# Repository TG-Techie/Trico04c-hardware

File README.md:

# Trico04c-hardware
published under : Attribution-NonCommercial 3.0 United States (CC BY-NC 3.0 US)

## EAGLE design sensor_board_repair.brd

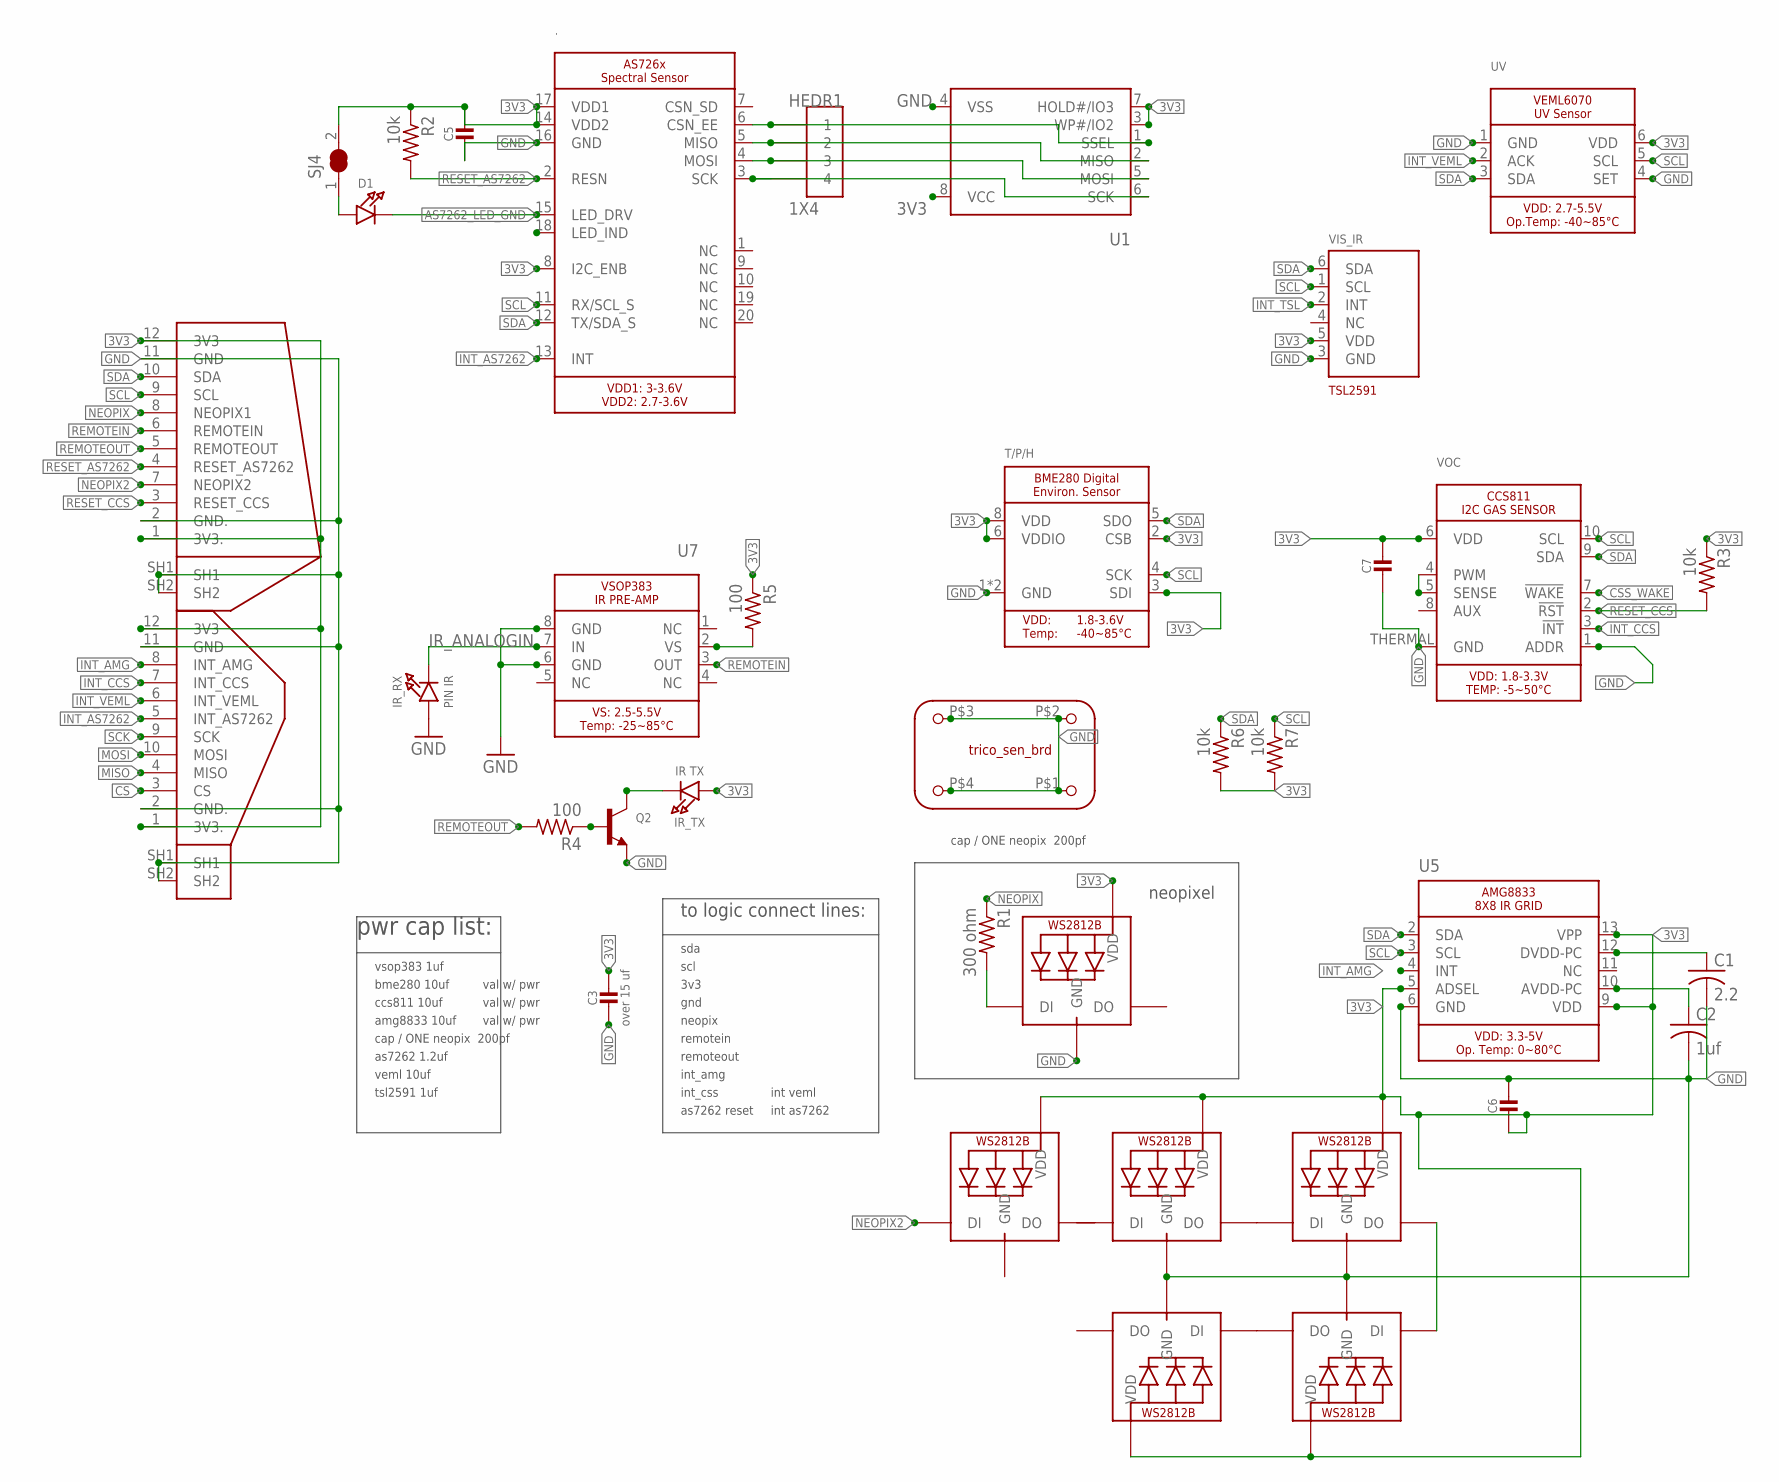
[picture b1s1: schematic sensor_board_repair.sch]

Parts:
.: SEN-SPECTRAL-AS726X-NEEDS_MEMORYEXTEN; MICROBUILDER_AS726X_LGA20_EXTENDED
.., ..., ...., ....., ......: WS2812B_5050N; WS2812B-NARROW
C1: 2.2; C0805
C2: 1uf; C0805
C3: over 15 uf; MICROBUILDER__0805
C5, C6, C7: C-US_0805-NOTHERMALS; MICROBUILDER_0805_NOTHERMALS
D1: LED-MICROBUILDER1206; MICROBUILDER_CHIPLED_1206
HEDR1: 1X4; 1X4_POGO
IR_RX: PIN IR; CHIPLED_1206
IR_TX: IR TX; CHIPLED_1206
LED1: LED-NEO-WS2812B5050; WS2812B
Q2: TRANSISTOR_NPNWIDE; SOT23-WIDE
R1: 300 ohm; R0805
R2, R3, R6, R7: 10k; R0805
R4, R5: 100; R0805
SJ4: JUMPER_CLOSEDTEMP; SOLDERJUMPER_CLOSEDWIRE
T/P/H: SEN-ENVIRO-BME280EXTEN_TG; MICROBUILDER_BME280-EXTENDED
U1: FLASH-SPI-FOR_ADA_AS7262; MICROBUILDER_09_NOV_2015_SOIC8_150MIL
U5: SEN-AMG8833-8X8THERMAL-ADAEXTEN; MICROBUILDER_AMG8833_EXTENDED
U7: IR-INTRFC-VSOP383EXTEN; VSOP383_EXTENDED
U$1: SEN_BRD_TRICO04C; TRICO04C_SEN_BRD
U$4: HEDR-SEN-I2CSLAVE_EXTEN; FPC_TE_1-1734839-2_EXTENDED
U$5: HEDR-SEN-INTSLAVE_EXTEN; FPC_TE_1-1734839-2_EXTENDED
UV: SEN-UV-I2C-VEML6070EXTEN; MICROBUILDER_VEML6070_EXTENDED
VIS_IR: SEN-LIGHT_LUX-HDR-TSL2591EXTEB; MICROBUILDER_DFN6_TAOS_EXTENDED
VOC: SEN-GAS-CCS811-PARTS/MILLIONEXTEN; MICROBUILDER_CCS811-EXTENDED

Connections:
3V3: ..8 (I2C_ENB), ..14 (VDD2), ..17 (VDD1), ...1-VDD (VDD), ....1-VDD (VDD), .....1-VDD (VDD), ......1-VDD (VDD), .......1-VDD (VDD), C3.1, C5.1, C6.2, C7.1, IR_TX.A, LED1.1-VDD (VDD), R2.1, R3.1, R5.1, R6.2, R7.2, SJ4.2, T/P/H.2 (CSB), T/P/H.3 (SDI), T/P/H.6 (VDDIO), T/P/H.8 (VDD), U1.3 (WP#/IO2), U1.7 (HOLD#/IO3), U1.8 (VCC), U5.5 (ADSEL), U5.9 (VDD), U5.13 (VPP), U$4.1 (3V3.), U$4.12 (3V3), U$5.1 (3V3.), U$5.12 (3V3), UV.6 (VDD), VIS_IR.5 (VDD), VOC.6 (VDD); also elsewhere on the board
AMGCAPAV: C1.1, C2.1, U5.10 (AVDD-PC), U5.12 (DVDD-PC)
AS7262_LED_GND: ..15 (LED_DRV), D1.C
CS: U$5.3 (CS)
CSS_WAKE: VOC.7 (!WAKE)
FLASH_CS: ..6 (CSN_EE), HEDR1.1, U1.1 (SSEL)
FLASH_MISO: ..5 (MISO), HEDR1.2, U1.2 (MISO)
FLASH_MOSI: ..4 (MOSI), HEDR1.3, U1.5 (MOSI)
FLASH_SCK: ..3 (SCK), HEDR1.4, U1.6 (SCK)
GND: ..16 (GND), ...3-GND (GND), ....3-GND (GND), .....3-GND (GND), ......3-GND (GND), .......3-GND (GND), C1.2, C2.2, C3.2, C5.2, C6.1, C7.2, IR_RX.A, LED1.3-GND (GND), Q2.2 (E), T/P/H.1 (GND), T/P/H.7 (GND), U1.4 (VSS), U5.6 (GND), U7.6 (GND), U7.8 (GND), U$1.P$1, U$1.P$2, U$1.P$3, U$1.P$4, U$4.2 (GND.), U$4.11 (GND), U$4.SH1, U$4.SH2, U$5.2 (GND.), U$5.11 (GND), U$5.SH1, U$5.SH2, UV.1 (GND), UV.4 (SET), VIS_IR.3 (GND), VOC.1 (ADDR), VOC.THERMAL (GND); also elsewhere on the board
INT_AMG: U5.4 (INT), U$5.8 (INT_AMG)
INT_AS7262: ..13 (INT), U$5.5 (INT_AS7262)
INT_CCS: U$5.7 (INT_CCS), VOC.3 (!INT)
INT_TSL: VIS_IR.2 (INT)
INT_VEML: U$5.6 (INT_VEML), UV.2 (ACK)
IR_ANALOGIN: IR_RX.C, U7.7 (IN)
MISO: U$5.4 (MISO)
MOSI: U$5.10 (MOSI)
unnamed: VOC.4 (PWM), VOC.5 (SENSE)
unnamed: D1.A, SJ4.1
unnamed: R5.2, U7.2 (VS)
unnamed: Q2.1 (B), R4.1
unnamed: ....2-DOUT (DO), .....4-DIN (DI)
unnamed: ...2-DOUT (DO), ....4-DIN (DI)
unnamed: ......2-DOUT (DO), .......4-DIN (DI)
unnamed: .....2-DOUT (DO), ......4-DIN (DI)
unnamed: LED1.4-DIN (DI), R1.2
unnamed: IR_TX.C, Q2.3 (C)
NEOPIX: R1.1, U$4.8 (NEOPIX1)
REMOTEIN: U7.3 (OUT), U$4.6 (REMOTEIN)
REMOTEOUT: R4.2, U$4.5 (REMOTEOUT)
RESET_AS7262: ..2 (RESN), R2.2, U$4.4 (RESET_AS7262)
RESET_CCS: R3.2, U$4.3 (RESET_CCS), VOC.2 (!RST)
SCK: U$5.9 (SCK)
SCL: ..11 (RX/SCL_S), R7.1, T/P/H.4 (SCK), U5.3 (SCL), U$4.9 (SCL), UV.5 (SCL), VIS_IR.1 (SCL), VOC.10 (SCL); also elsewhere on the board
SDA: ..12 (TX/SDA_S), R6.1, T/P/H.5 (SDO), U5.2 (SDA), U$4.10 (SDA), UV.3 (SDA), VIS_IR.6 (SDA), VOC.9 (SDA); also elsewhere on the board

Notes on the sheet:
neopixel
pwr cap list:
vsop383 1uf
bme280 10uf
ccs811 10uf
amg8833 10uf
val w/ pwr
cap / ONE neopix 200pf
to logic connect lines:
sda
scl
3v3
gnd
neopix
remotein
remoteout
int_amg
int_css
as7262 1.2uf
as7262 reset
int as7262
int veml
veml 10uf
tsl2591 1uf

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
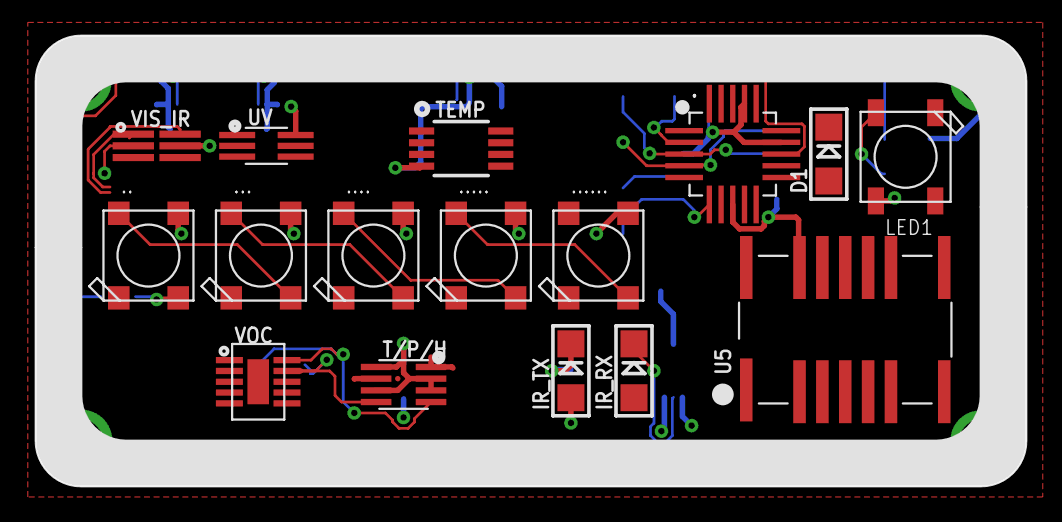
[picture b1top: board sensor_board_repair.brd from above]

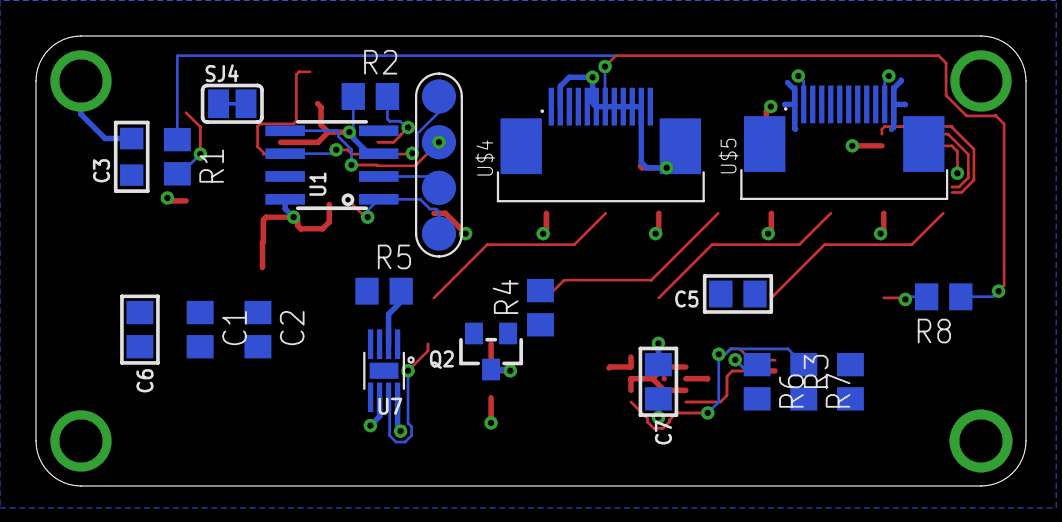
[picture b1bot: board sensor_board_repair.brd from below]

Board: 2 copper layers, 55.0 x 25.0 mm, 38 parts (21 on the bottom side), 32 nets.

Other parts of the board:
R8: 300 ohm; R0805
TEMP: SEN-TEMP-PERCISE-I2C-MCP9808-E/MS; MICROBUILDER_MSOP8_0.65MM

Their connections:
3V3: TEMP.8; also elsewhere on the board
GND: TEMP.4, TEMP.5, TEMP.6, TEMP.7; also elsewhere on the board
SCL: TEMP.2; also elsewhere on the board
SDA: TEMP.1; also elsewhere on the board

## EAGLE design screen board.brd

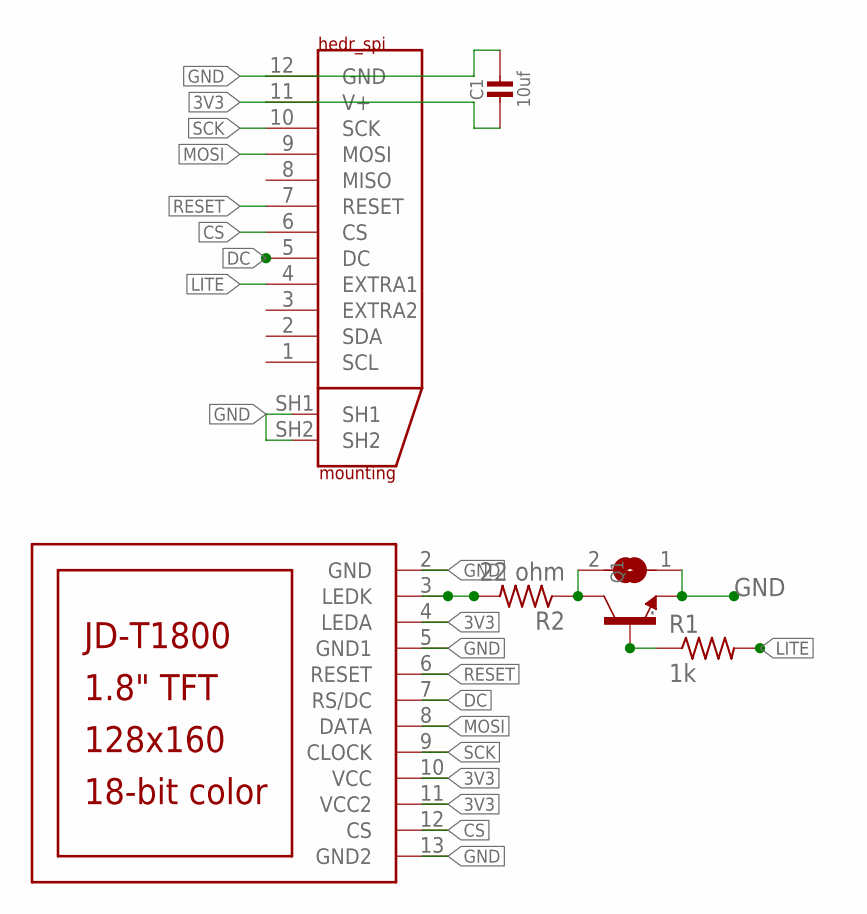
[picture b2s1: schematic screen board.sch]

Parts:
.: JUMPER_OPEN; SOLDERJUMPER_ARROW_NOPASTE
..: HEDR-SPI-PFC_12SLAVE_EXTEN; FPC_TE_1-1734839-2_EXTENDED
C1: 10uf; MICROBUILDER_0805_NOTHERMALS
LCD2: TFT-1.8-JD-T1800-_NO_DRILL_WRAP; 0TG-LIB-V01.1_JD-T1800-REV-WRAP_NO-DRILL
Q1: TRANSISTOR_NPNWIDE; SOT23-WIDE
R1: 1k; R0805
R2: 22 ohm; R0805

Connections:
3V3: ...11 (V+), C1.2, LCD2.4 (LEDA), LCD2.10 (VCC), LCD2.11 (VCC2)
CS: ...6 (CS), LCD2.12 (CS)
DC: ...5 (DC), LCD2.7 (RS/DC)
GND: ..1, ...12 (GND), ...SH1, ...SH2, C1.1, LCD2.2 (GND), LCD2.5 (GND1), LCD2.13 (GND2), Q1.2 (E)
LITE: ...4 (EXTRA1), R1.2
MOSI: ...9 (MOSI), LCD2.8 (DATA)
unnamed: Q1.1 (B), R1.1
unnamed: LCD2.3 (LEDK), R2.2
unnamed: ..2, Q1.3 (C), R2.1
RESET: ...7 (RESET), LCD2.6 (RESET)
SCK: ...10 (SCK), LCD2.9 (CLOCK)

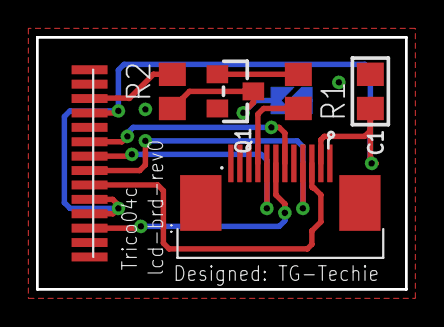
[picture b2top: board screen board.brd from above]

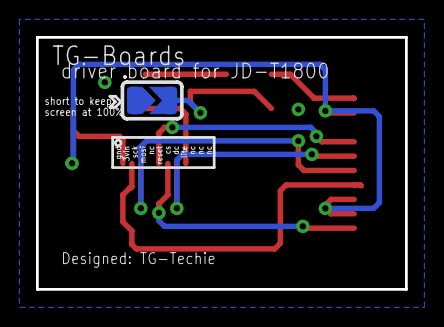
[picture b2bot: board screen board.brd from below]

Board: 2 copper layers, 20.5 x 14.0 mm, 7 parts (2 on the bottom side), 11 nets.

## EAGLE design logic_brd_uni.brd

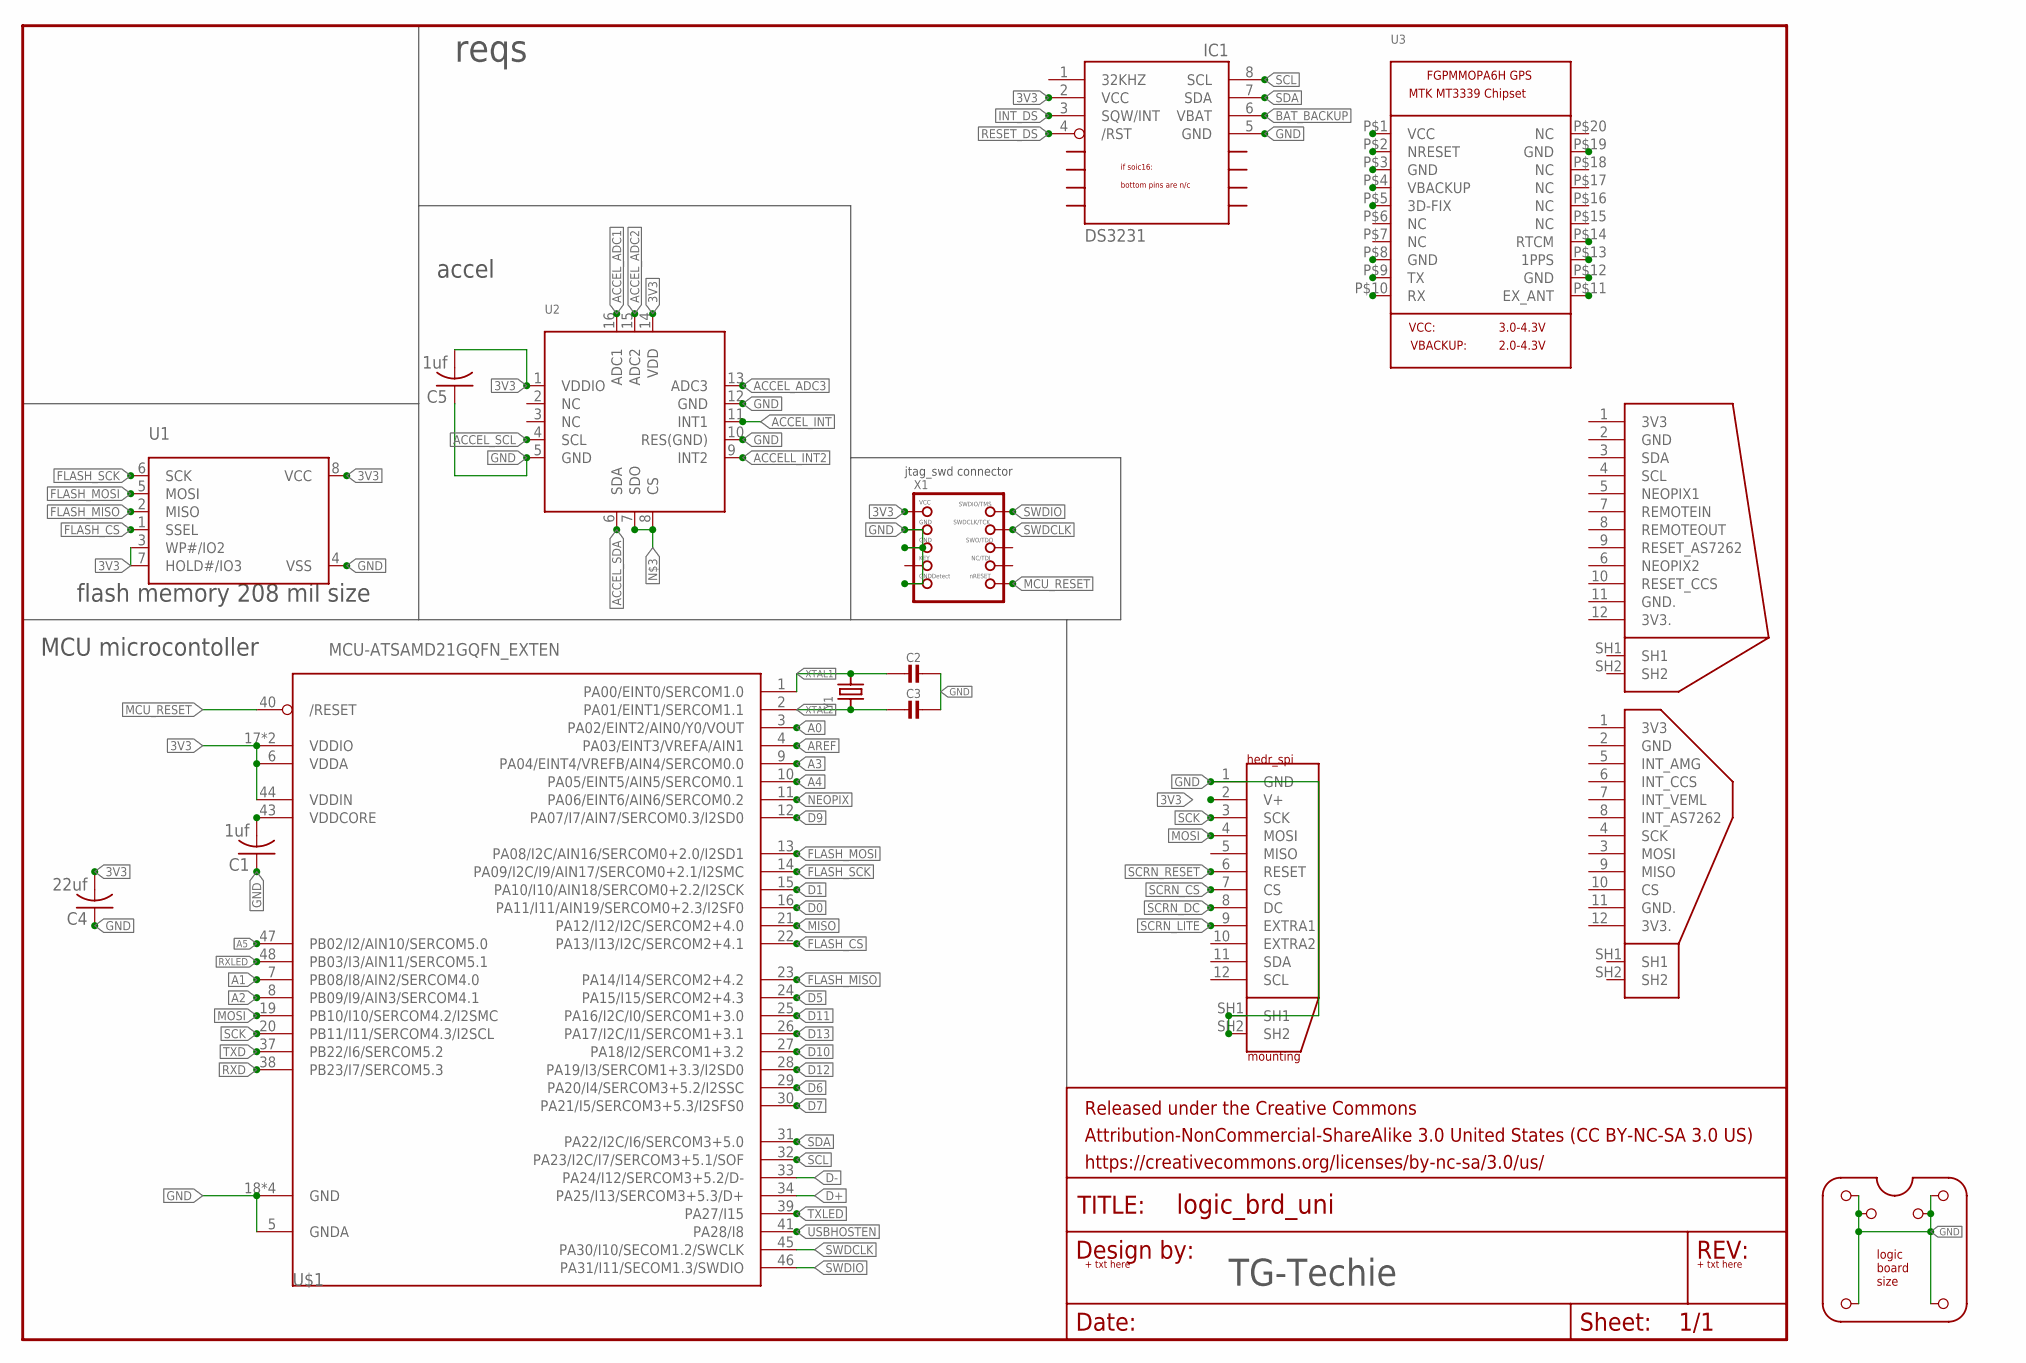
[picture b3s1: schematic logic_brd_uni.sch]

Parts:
C1, C5: 1uf; C0805K
C2, C3: C-US_0805-NOOUTLINE; MICROBUILDER_0805-NO
C4: 22uf; C0805K
FRAME1: LEDGER-TG-TECHIE-STANDARDNO_PACKAGE; DUMMY
IC1: SEN-TIME-DS3231-(PERSICION-TEMP); SOIC8_150MIL
U1: SPIFLASH_SOIC8208MIL; SOIC8_208MIL
U2: ACCEL_LIS3DHTREXTEN; LGA16_3X3MM_EXTENDED
U3: GPS-ADA-V3-FGPMMOPA6HEXTEN; MICROBUILDER_FGPMMOPA6H_EXTENDED
U$1: MCU-ATSAMD21GQFN_EXTEN; TQFN48_7MM_EXTENDED
U$2: LOGIC-BRD; LOGIC-BOARD
U$3: HEDR-SEN-I2CMASTER_EXTEN; FPC_TE_1-1734839-2_EXTENDED
U$4: HEDR-SEN-INTMASTER_EXTEN; FPC_TE_1-1734839-2_EXTENDED
U$5: HEDR-SPI-FPC_12MASTER_EXTEN; 0TG-LIB-V01.1_FPC_TE_1-1734839-2_EXTENDED
X1: INTRFC-JTAG-CORTEXBOXPOSTS; 2X05_1.27MM_BOX_POSTS
Y1: XTAL_ADA4.9X1.8; MICROBUILDER_CRYSTAL_4.9X1.8

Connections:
3V3: C4.2, C5.2, IC1.2 (VCC), U1.3 (WP#/IO2), U1.7 (HOLD#/IO3), U1.8 (VCC), U2.1 (VDDIO), U2.14 (VDD), U$1.6 (VDDA), U$1.17 (VDDIO), U$1.36 (VDDIO), U$1.44 (VDDIN), U$5.2 (V+), X1.1 (VCC)
A0: U$1.3 (PA02/EINT2/AIN0/Y0/VOUT)
A1: U$1.7 (PB08/I8/AIN2/SERCOM4.0)
A2: U$1.8 (PB09/I9/AIN3/SERCOM4.1)
A3: U$1.9 (PA04/EINT4/VREFB/AIN4/SERCOM0.0)
A4: U$1.10 (PA05/EINT5/AIN5/SERCOM0.1)
A5: U$1.47 (PB02/I2/AIN10/SERCOM5.0)
ACCELL_INT2: U2.9 (INT2)
ACCEL_ADC1: U2.16 (ADC1)
ACCEL_ADC2: U2.15 (ADC2)
ACCEL_ADC3: U2.13 (ADC3)
ACCEL_INT: U2.11 (INT1)
ACCEL_SCL: U2.4 (SCL)
ACCEL_SDA: U2.6 (SDA)
AREF: U$1.4 (PA03/EINT3/VREFA/AIN1)
BAT_BACKUP: IC1.6 (VBAT)
D0: U$1.16 (PA11/I11/AIN19/SERCOM0+2.3/I2SF0)
D1: U$1.15 (PA10/I10/AIN18/SERCOM0+2.2/I2SCK)
D5: U$1.24 (PA15/I15/SERCOM2+4.3)
D6: U$1.29 (PA20/I4/SERCOM3+5.2/I2SSC)
D7: U$1.30 (PA21/I5/SERCOM3+5.3/I2SFS0)
D9: U$1.12 (PA07/I7/AIN7/SERCOM0.3/I2SD0)
D10: U$1.27 (PA18/I2/SERCOM1+3.2)
D11: U$1.25 (PA16/I2C/I0/SERCOM1+3.0)
D12: U$1.28 (PA19/I3/SERCOM1+3.3/I2SD0)
D13: U$1.26 (PA17/I2C/I1/SERCOM1+3.1)
D+: U$1.34 (PA25/I13/SERCOM3+5.3/D+)
D-: U$1.33 (PA24/I12/SERCOM3+5.2/D-)
FLASH_CS: U1.1 (SSEL), U$1.22 (PA13/I13/I2C/SERCOM2+4.1)
FLASH_MISO: U1.2 (MISO), U$1.23 (PA14/I14/SERCOM2+4.2)
FLASH_MOSI: U1.5 (MOSI), U$1.13 (PA08/I2C/AIN16/SERCOM0+2.0/I2SD1)
FLASH_SCK: U1.6 (SCK), U$1.14 (PA09/I2C/I9/AIN17/SERCOM0+2.1/I2SMC)
GND: C1.1, C2.1, C3.1, C4.1, C5.1, IC1.5 (GND), U1.4 (VSS), U2.5 (GND), U2.10 (RES(GND)), U2.12 (GND), U$1.5 (GNDA), U$1.18 (GND), U$1.35 (GND), U$1.42 (GND), U$1.THERMAL (GND), U$2.P$1, U$2.P$2, U$2.P$3, U$2.P$4, U$2.P$5, U$2.P$6, U$5.1 (GND), U$5.SH1, U$5.SH2, X1.3 (GND), X1.5 (GND), X1.9 (GNDDETECT)
INT_DS: IC1.3 (SQW/INT)
MCU_RESET: U$1.40 (/RESET), X1.10 (NRESET)
MISO: U$1.21 (PA12/I12/I2C/SERCOM2+4.0)
MOSI: U$1.19 (PB10/I10/SERCOM4.2/I2SMC), U$5.4 (MOSI)
unnamed: C1.2, U$1.43 (VDDCORE)
unnamed: U2.7 (SDO), U2.8 (CS)
NEOPIX: U$1.11 (PA06/EINT6/AIN6/SERCOM0.2)
RESET_DS: IC1.4 (/RST)
RXD: U$1.38 (PB23/I7/SERCOM5.3)
RXLED: U$1.48 (PB03/I3/AIN11/SERCOM5.1)
SCK: U$1.20 (PB11/I11/SERCOM4.3/I2SCL), U$5.3 (SCK)
SCL: IC1.8 (SCL), U$1.32 (PA23/I2C/I7/SERCOM3+5.1/SOF)
SCRN_CS: U$5.7 (CS)
SCRN_DC: U$5.8 (DC)
SCRN_LITE: U$5.9 (EXTRA1)
SCRN_RESET: U$5.6 (RESET)
SDA: IC1.7 (SDA), U$1.31 (PA22/I2C/I6/SERCOM3+5.0)
SWDCLK: U$1.45 (PA30/I10/SECOM1.2/SWCLK), X1.4 (SWDCLK)
SWDIO: U$1.46 (PA31/I11/SECOM1.3/SWDIO), X1.2 (SWDIO)
TXD: U$1.37 (PB22/I6/SERCOM5.2)
TXLED: U$1.39 (PA27/I15)
USBHOSTEN: U$1.41 (PA28/I8)
XTAL1: C2.2, U$1.1 (PA00/EINT0/SERCOM1.0), Y1.2
XTAL2: C3.2, U$1.2 (PA01/EINT1/SERCOM1.1), Y1.1

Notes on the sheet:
MCU microcontoller
accel
flash memory 208 mil size
reqs
TG-Techie
jtag_swd connector

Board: 2 copper layers, 17 parts (0 on the bottom side), 17 nets, no tracks yet.

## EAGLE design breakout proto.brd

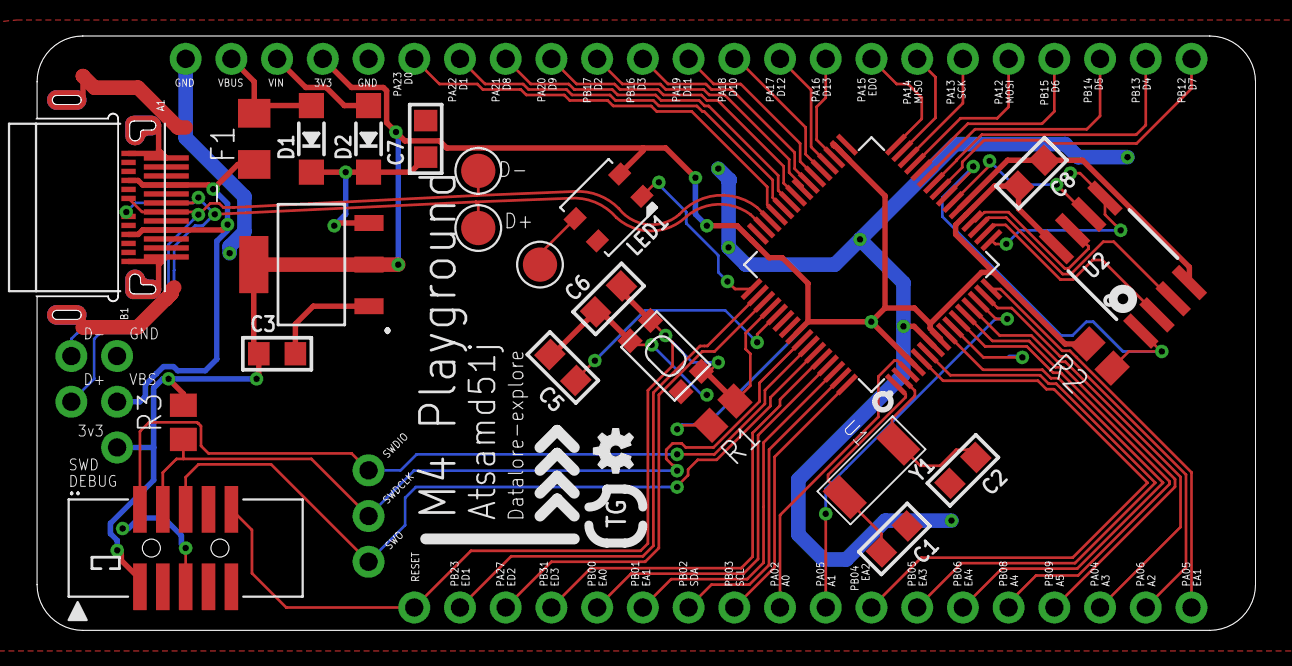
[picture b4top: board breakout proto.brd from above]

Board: 2 copper layers, 67.7 x 33.0 mm, 51 parts (1 on the bottom side), 59 nets.

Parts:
.: VREG-1.5A-3.3V-ADP3339AKCZ-3.3-RL; SOT230P700X180-4N
..: 2X05_1.27MM_BOX_POSTS
C1, C2: 22pf; MICROBUILDER__0805
C3, C7, C8: 1uf; MICROBUILDER__0805
C5: 4.7uf; MICROBUILDER__0805
C6: .1uf; MICROBUILDER__0805
D1, D2: SOD-123
F1: R1206
FRAME1: FRAME-LEDGER; CREATIVE_COMMONS
HEDR1, HEDR2, HEDR4, HEDR5, HEDR8, HEDR10, HEDR11: 1X2HEDR; 1X2_HEDR
HEDR3, HEDR7, HEDR9: 1X4HEDR; 1X4_HEDR
HEDR6: 1X5HEDR; 1X5_HEDR
LED1: LED-NEO-WS2812B3535; LED3535
LOGO1: OSHW-LOGOMINI; OSHW-LOGO-MINI
R1, R2, R3: 10k; R0805
SW1: SPST_TACT-KMR2; KMR2
TP1: TESTPOINT_1X1; 1X1_POGO
U1: MCU-ATSAMD51J; QFP50P1200X1200X120-64N
U2: SOIC8_208MIL
U$1, U$3, U$5, U$6, U$7, U$9, U$11, U$12, U$16: 1X1HEDR; 1X1_HEDR
U$2, U$4, U$10: 1X3HEDR; 1X3_HEDR
U$8, U$13, U$14: 1X1POGO; 1X1_POGO
U$15: LOGO_TG_TEST_LARGE
Y1: 32.768; MICROBUILDER_CRYSTAL_4.9X1.8
_: USB-C-CON-MIDBRD-SHORT-1-2295018-2EXTEN; TE_1-2295018-2_EXTEN

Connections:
3V3: ..2, ..4, ...1, C3.1, C8.2, HEDR6.4, LED1.2, R1.2, R2.2, R3.2, U1.4, U1.8, U1.21, U1.34, U1.48, U1.56, U2.8, U$16.1
A0: U1.3, U$1.1
A1: U1.14, U$11.1
A2: U1.15, U$10.2
A3: U1.13, U$10.3
A4: U1.11, U$2.2
A5: U1.12, U$2.3
D0: HEDR9.1, U1.44
D1: HEDR9.2, U1.43
D2: HEDR4.2, U1.40
D3: HEDR4.1, U1.39
D4: HEDR3.2, U1.26
D5: HEDR3.3, U1.27
D6: HEDR3.4, U1.28
D7: HEDR3.1, U1.25
D8: HEDR9.3, U1.42
D9: HEDR9.4, U1.41
D10: HEDR7.2, U1.37
D11: HEDR7.1, U1.38
D12: HEDR7.3, U1.36
D13: HEDR7.4, U1.35
D+: HEDR11.2, U1.46, U$14.1, _.A6, _.B6
D-: HEDR11.1, U1.45, U$13.1, _.A7, _.B7
EA0: HEDR5.1, U1.61
EA1: HEDR5.2, U1.62
EA2: HEDR2.1, U1.5
EA3: HEDR2.2, U1.6
EA4: U1.9, U$2.1
EA5: U1.16, U$10.1
ED0: U1.32, U$5.1
ED1: U1.50, U$7.1
ED2: U1.51, U$6.1
ED3: U1.60, U$3.1
FLASH_CS: R2.1, U1.24, U2.1
FLASH_IO0: U1.17, U2.5
FLASH_IO1: U1.18, U2.2
FLASH_IO2: U1.19, U2.3
FLASH_IO3: U1.20, U2.7
FLASH_SCK: U1.23, U2.6
GND: ..1, ...3, ...5, C1.1, C2.2, C3.2, C5.2, C6.1, C7.2, C8.1, HEDR6.1, HEDR6.5, HEDR10.2, LED1.4, SW1.2, SW1.4, U1.7, U1.22, U1.33, U1.47, U1.54, U2.4, _.A1, _.A12, _.B1, _.B12, _.S1, _.S2, _.S3, _.S4
MISO: U1.31, U$4.1
MOSI: U1.29, U$4.3
unnamed: C5.1, U1.53
unnamed: C1.2, U1.1, Y1.2
unnamed: C2.1, U1.2, Y1.1
NEOPIX: LED1.1, U1.49
NEOPIX_DOUT: LED1.3, TP1.1
RESET: ...10, C6.2, R1.1, SW1.1, SW1.3, U1.52, U$9.1
SCK: U1.30, U$4.2
SCL: HEDR1.2, U1.64
SDA: HEDR1.1, U1.63
SWDCLK: ...4, HEDR8.2, R3.1, U1.57
SWDIO: ...2, HEDR8.1, U1.58
SWO: ...6, U1.59, U$12.1
USB_HOSTEN: U1.10, U$8.1
VBUS: D1.A, F1.2, HEDR6.2
VBUS_RAW: F1.1, HEDR10.1, _.A4, _.A9, _.B4, _.B9
VIN: D2.A, HEDR6.3
VSORS: ..3, C7.1, D1.C, D2.C

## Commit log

2018-05-28 052718- finished m4 proto boards
2018-05-28 052818 - update board proto
2018-05-31 removed datalore+

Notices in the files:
parts and their libraries:
SparkFun-Aesthetics: Licensing: Creative Commons ShareAlike 4.0 International - https://creativecommons.org/licenses/by-sa/4.0
SparkFun-Aesthetics: Released under the Creative Commons Attribution Share-Alike 4.0 License
SparkFun-Aesthetics: https://creativecommons.org/licenses/by-sa/4.0
